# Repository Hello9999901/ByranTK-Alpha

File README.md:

# ByranTK-Alpha

# Note: New 3D Printed Version of the case added! First prototype working!!

*The ByranTK-Alpha is an 80 key custom mechanical keyboard, designed to be made with any material.*
<br>
<br>
*"All the keys you need and no more."*

### V1.1 is confirmed to be working with firmware from https://github.com/Hello9999901/zmk-config-btk-alpha

# What is it:
The ByranTK-Alpha is an ongoing open-source keyboard project. It is extremely simple and utilizes a nice!nano from Nice Keyboards as the MCU. The battery life is estimated to be around 3 months of continuous usage (varies extremely depending on battery capacity, tested with 500mah battery from Adafruit). The keyboard is designed in KiCAD and FreeCAD, with the renders made with Blender.

# Features:
 - ZMK Firmware
 - Pro Micro Form Factor *
 - Wireless First Design
 - Split Spacebar
 - Low Profile (relative to other keyboards)
 - Hotswap Sockets
 - South facing (supports cherry profile)
 - Exploded 75% (ish) layout
 - Highly Customizable

# Why?
Because nobody has done such thing yet. I have always wanted a simple-looking, customizable (software-wise and hardware-wise), exploded 75% layout keyboard. In addition, it had to be under a certain price point. I estimate for it to cost less than 100 dollars for all the parts and all the machining, though that is subject to change. If you want CNC alu, then that'll cost you a couple cold hard Benjamins (tldr; a lot).

# Image Gallery
(subject to change as design alters)
<div style="display: flex;">

</div>

# Build Guide
### This build guide is very vague and will be improved on in the near future
### Parts:
> Note that these part links are only for reference. Some products can be found for cheaper (especially the hotswap sockets).

> The SPDT and SPST switches have specific footprints that match on the board. You can alter them if they're out of stock.

> You don't need to buy diodes if you are using SMT assembly. I used JLCPCB.
  - PCB
  - [Kailh Hotswap Sockets](https://shop.keyboard.io/products/kailh-hotswap-sockets-for-mx-style-keyswitches-x-25)
  - [Diodes (1N4148 SMT SOD-123)](https://www.adafruit.com/product/5099)
  - [SPDT Switch](https://www.adafruit.com/product/805)
  - [Battery (can be different capacity) with JST-PH 2 Pin Header](https://www.adafruit.com/product/1578)
  - [SPST Switch](https://www.adafruit.com/product/1489)
  - [JST-PH Right Angle Connector](https://www.adafruit.com/product/1769)
  - [Swiss Socket Headers (Female)](https://www.adafruit.com/product/3646)
  - [Swiss Socket Headers (Male)](https://www.adafruit.com/product/3647)

1. Order all the parts
   - I ordered everything off of JLCPCB, with SMT assembly for the diodes because I'm lazy. The pick and place/bom files are in the bom folder, ready for upload to JLCPCB. It is highly suggested you use SMT assembly because it is extremely cheap and saves a lot of time.
   - Apparantly, you can also get smt hotswap sockets assembled too, though I did not do that.
2. Solder it all together
   - Solder on the hotswap sockets and the nice!nano. This will take a while (perhaps an hour or two) depending on your soldering experience. Note that if you choose not to use SMT assembly on the PCB, the diodes will be very hard to solder. I socketed the nice!nano using Swiss machine pins off of Adafruit.
3. Build and flash the firmware onto the nice!nano
   - Build the firmware and put the nice!nano into bootloader (DFU) mode (short GND and RST twice in rapid succession). Drag the UF2 file into the nice!nano "storage device". The firmware can be made with my zmk-config directory.
4. Laser cut the case or 3D print
   - This step is pretty self explanatory. It's a sandwich design, so lasercut many pieces and adhere them together. The plate must be 1.5mm (+- 0.1mm). The rest can be any height as long as when everything is stacked together, it is taller than 15mm, and the height between the bottom of the plate and the top of the bottom pice is taller than 12mm.
   - Alternatively, you can 3D print the case. I decided to 3D print because it was faster to prototype. 2 file types, one split and one full depending on your bed size. It also looks really cool.
5. Put everything together
   - Glue it, screw it together, I don't really know. I screwed into a 3D printed case with some screws found in a bin of hope. Just make sure the entire thing fits. If you're that type of person, the more FLeX the better. Nylon should get you that. Plug in the battery (you might need to switch the battery wiring to make sure the GND goes into GND and RAW goes into RAW). You don't need screws to hold the PCB and plate together; the hotswap sockets and the plate should hold itself together. Get some 5mm foam and put it as dampener under the PCB. Make sure to keep the battery isolated when dampening so it doesn't short/blow up.
6. Use it
   - You've made it! Congrats! Customize the keymap, change the case material, it's all up to you. That's the beauty of open source hardware and software. I hope you enjoy the ByranTK-Alpha.

# License
Unless stated otherwise, the parts are licensed under the MIT License. Parts that are identified as (GPL) are licensed under the GPLv3 License.

\* The nice!nano v2 is used in this design. It has 3 extra pins in the center of the PCB, two of which the ByranTK-Alpha utilizes

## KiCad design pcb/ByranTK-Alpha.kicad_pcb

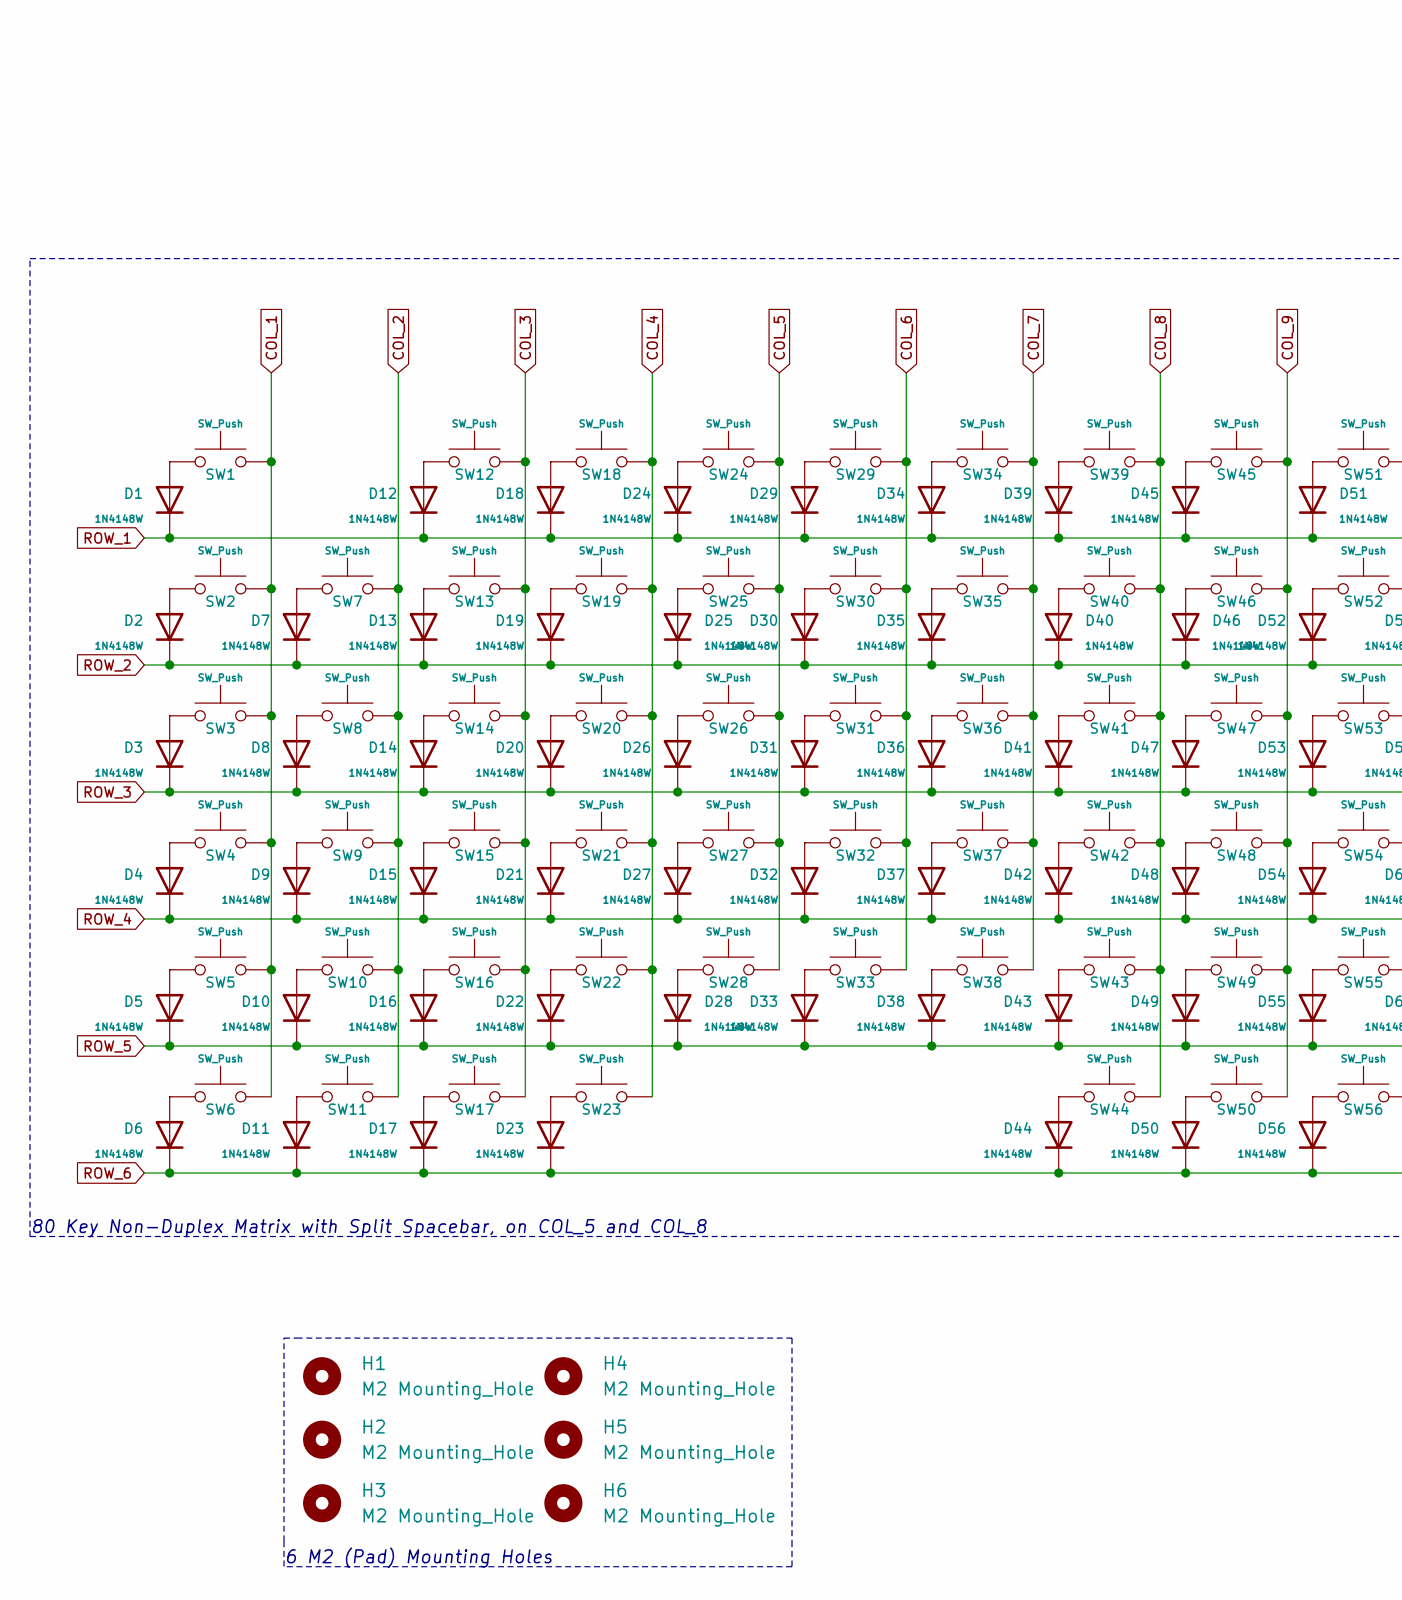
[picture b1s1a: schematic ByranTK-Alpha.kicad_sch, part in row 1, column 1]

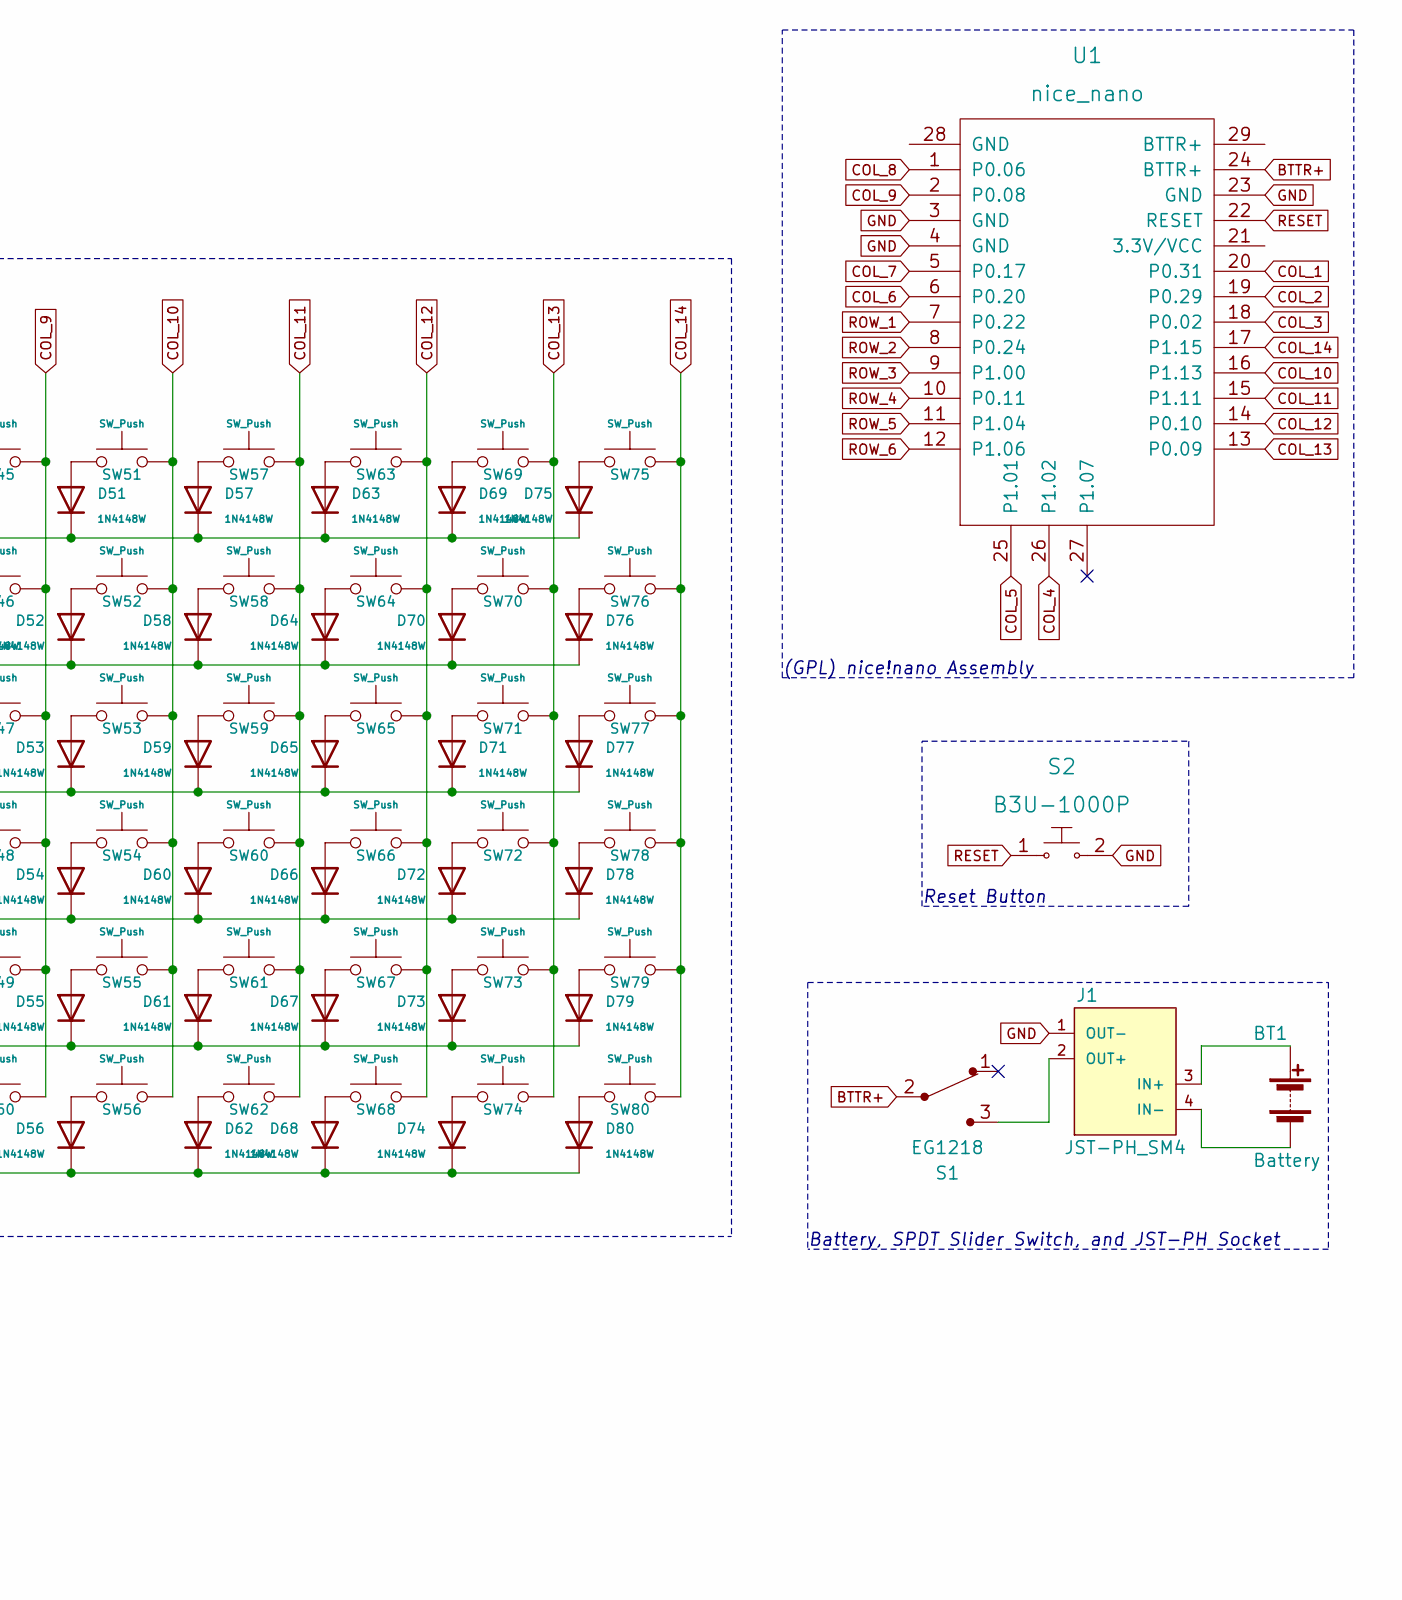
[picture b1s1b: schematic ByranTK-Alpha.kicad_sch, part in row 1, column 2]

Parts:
BT1: Battery; ADAFRUIT_BAT_ID_1570_100mAh
D1, D2, D3, D4, D5, D6, D7, D8, D9, D10, D11, D12, D13, D14, D15, D16, D17, D18, D19, D20, D21, D22, D23, D24, D25, D26, D27, D28, D29, D30, D31, D32, D33, D34, D35, D36, D37, D38, D39, D40, D41, D42, D43, D44, D45, D46, D47, D48, D49, D50, D51, D52, D53, D54, D55, D56, D57, D58, D59, D60, D61, D62, D63, D64, D65, D66, D67, D68, D69, D70, D71, D72, D73, D74, D75, D76, D77, D78, D79, D80: 1N4148W; D_SOD-123
H1, H2, H3, H4, H5, H6: M2 Mounting_Hole; MountingHole_2.2mm_M2_Pad
J1: JST-PH_SM4; JST_PH_S2B-PH-SM4-TB_1x02-1MP_P2.00mm_Horizontal
S1: EG1218; Switch_Slide_11.6x4mm_EG1218; MPN EG1218; Digi-Key_PN EG1903-ND
S2: B3U-1000P; Switch_Tactile_SMD_B3U-1000P; MPN B3U-1000P; Digi-Key_PN SW1020CT-ND
SW1, SW2, SW7, SW8, SW9, SW10, SW12, SW13, SW14, SW15, SW16, SW18, SW19, SW20, SW21, SW22, SW24, SW25, SW26, SW27, SW28, SW29, SW30, SW31, SW32, SW33, SW34, SW35, SW36, SW37, SW38, SW39, SW40, SW41, SW42, SW43, SW45, SW46, SW47, SW48, SW49, SW50, SW51, SW52, SW53, SW54, SW55, SW56, SW57, SW58, SW59, SW60, SW61, SW62, SW63, SW64, SW65, SW66, SW68, SW69, SW70, SW71, SW73, SW74, SW75, SW78, SW79, SW80: SW_Push; MXOnly-1U-Hotswap
SW3, SW77: SW_Push; MXOnly-1.5U-Hotswap
SW4, SW67: SW_Push; MXOnly-1.75U-Hotswap
SW5, SW72: SW_Push; MXOnly-2.25U-Hotswap
SW6, SW11, SW17: SW_Push; MXOnly-1.25U-Hotswap
SW23, SW44: SW_Push; MXOnly-2.75U-Hotswap
SW76: SW_Push; MXOnly-2U-Hotswap
U1: nice_nano

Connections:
BTTR+: S1.2, U1.24 (BTTR+)
COL_1: SW1.2, SW2.2, SW3.2, SW4.2, SW5.2, SW6.2, U1.20 (P0.31)
COL_2: SW7.2, SW8.2, SW9.2, SW10.2, SW11.2, U1.19 (P0.29)
COL_3: SW12.2, SW13.2, SW14.2, SW15.2, SW16.2, SW17.2, U1.18 (P0.02)
COL_4: SW18.2, SW19.2, SW20.2, SW21.2, SW22.2, SW23.2, U1.26 (P1.02)
COL_5: SW24.2, SW25.2, SW26.2, SW27.2, SW28.2, U1.25 (P1.01)
COL_6: SW29.2, SW30.2, SW31.2, SW32.2, SW33.2, U1.6 (P0.20)
COL_7: SW34.2, SW35.2, SW36.2, SW37.2, SW38.2, U1.5 (P0.17)
COL_8: SW39.2, SW40.2, SW41.2, SW42.2, SW43.2, SW44.2, U1.1 (P0.06)
COL_9: SW45.2, SW46.2, SW47.2, SW48.2, SW49.2, SW50.2, U1.2 (P0.08)
COL_10: SW51.2, SW52.2, SW53.2, SW54.2, SW55.2, SW56.2, U1.16 (P1.13)
COL_11: SW57.2, SW58.2, SW59.2, SW60.2, SW61.2, SW62.2, U1.15 (P1.11)
COL_12: SW63.2, SW64.2, SW65.2, SW66.2, SW67.2, SW68.2, U1.14 (P0.10)
COL_13: SW69.2, SW70.2, SW71.2, SW72.2, SW73.2, SW74.2, U1.13 (P0.09)
COL_14: SW75.2, SW76.2, SW77.2, SW78.2, SW79.2, SW80.2, U1.17 (P1.15)
GND: J1.1 (OUT-), S2.2, U1.3 (GND), U1.4 (GND), U1.23 (GND)
unnamed: D1.2 (A), SW1.1
unnamed: D2.2 (A), SW2.1
unnamed: D3.2 (A), SW3.1
unnamed: D4.2 (A), SW4.1
unnamed: D5.2 (A), SW5.1
unnamed: D6.2 (A), SW6.1
unnamed: D7.2 (A), SW7.1
unnamed: D8.2 (A), SW8.1
unnamed: D9.2 (A), SW9.1
unnamed: D10.2 (A), SW10.1
unnamed: D11.2 (A), SW11.1
unnamed: D12.2 (A), SW12.1
unnamed: D13.2 (A), SW13.1
unnamed: D14.2 (A), SW14.1
unnamed: D15.2 (A), SW15.1
unnamed: D16.2 (A), SW16.1
unnamed: D17.2 (A), SW17.1
unnamed: D18.2 (A), SW18.1
unnamed: D19.2 (A), SW19.1
unnamed: D20.2 (A), SW20.1
unnamed: D21.2 (A), SW21.1
unnamed: D22.2 (A), SW22.1
unnamed: D23.2 (A), SW23.1
unnamed: D24.2 (A), SW24.1
unnamed: D25.2 (A), SW25.1
unnamed: D26.2 (A), SW26.1
unnamed: D27.2 (A), SW27.1
unnamed: D28.2 (A), SW28.1
unnamed: D29.2 (A), SW29.1
unnamed: D30.2 (A), SW30.1
unnamed: D31.2 (A), SW31.1
unnamed: D32.2 (A), SW32.1
unnamed: D33.2 (A), SW33.1
unnamed: D34.2 (A), SW34.1
unnamed: D35.2 (A), SW35.1
unnamed: D36.2 (A), SW36.1
unnamed: D37.2 (A), SW37.1
unnamed: D38.2 (A), SW38.1
unnamed: D39.2 (A), SW39.1
unnamed: D40.2 (A), SW40.1
unnamed: D41.2 (A), SW41.1
unnamed: D42.2 (A), SW42.1
unnamed: D43.2 (A), SW43.1
unnamed: D44.2 (A), SW44.1
unnamed: D45.2 (A), SW45.1
unnamed: D46.2 (A), SW46.1
unnamed: D47.2 (A), SW47.1
unnamed: D48.2 (A), SW48.1
unnamed: D49.2 (A), SW49.1
unnamed: D50.2 (A), SW50.1
unnamed: D51.2 (A), SW51.1
unnamed: D52.2 (A), SW52.1
unnamed: D53.2 (A), SW53.1
unnamed: D54.2 (A), SW54.1
unnamed: D55.2 (A), SW55.1
unnamed: D56.2 (A), SW56.1
unnamed: D57.2 (A), SW57.1
unnamed: D58.2 (A), SW58.1
unnamed: D59.2 (A), SW59.1
unnamed: D60.2 (A), SW60.1
unnamed: D61.2 (A), SW61.1
unnamed: D62.2 (A), SW62.1
unnamed: D63.2 (A), SW63.1
unnamed: D64.2 (A), SW64.1
unnamed: D65.2 (A), SW65.1
unnamed: D66.2 (A), SW66.1
unnamed: D67.2 (A), SW67.1
unnamed: D68.2 (A), SW68.1
unnamed: D69.2 (A), SW69.1
unnamed: D70.2 (A), SW70.1
unnamed: D71.2 (A), SW71.1
unnamed: D72.2 (A), SW72.1
unnamed: D73.2 (A), SW73.1
unnamed: D74.2 (A), SW74.1
unnamed: D75.2 (A), SW75.1
unnamed: D76.2 (A), SW76.1
unnamed: D77.2 (A), SW77.1
unnamed: D78.2 (A), SW78.1
unnamed: D79.2 (A), SW79.1
unnamed: D80.2 (A), SW80.1
unnamed: J1.2 (OUT+), S1.3
RESET: S2.1, U1.22 (RESET)
ROW_1: D1.1 (K), D12.1 (K), D18.1 (K), D24.1 (K), D29.1 (K), D34.1 (K), D39.1 (K), D45.1 (K), D51.1 (K), D57.1 (K), D63.1 (K), D69.1 (K), D75.1 (K), U1.7 (P0.22)
ROW_2: D2.1 (K), D7.1 (K), D13.1 (K), D19.1 (K), D25.1 (K), D30.1 (K), D35.1 (K), D40.1 (K), D46.1 (K), D52.1 (K), D58.1 (K), D64.1 (K), D70.1 (K), D76.1 (K), U1.8 (P0.24)
ROW_3: D3.1 (K), D8.1 (K), D14.1 (K), D20.1 (K), D26.1 (K), D31.1 (K), D36.1 (K), D41.1 (K), D47.1 (K), D53.1 (K), D59.1 (K), D65.1 (K), D71.1 (K), D77.1 (K), U1.9 (P1.00)
ROW_4: D4.1 (K), D9.1 (K), D15.1 (K), D21.1 (K), D27.1 (K), D32.1 (K), D37.1 (K), D42.1 (K), D48.1 (K), D54.1 (K), D60.1 (K), D66.1 (K), D72.1 (K), D78.1 (K), U1.10 (P0.11)
ROW_5: D5.1 (K), D10.1 (K), D16.1 (K), D22.1 (K), D28.1 (K), D33.1 (K), D38.1 (K), D43.1 (K), D49.1 (K), D55.1 (K), D61.1 (K), D67.1 (K), D73.1 (K), D79.1 (K), U1.11 (P1.04)
ROW_6: D6.1 (K), D11.1 (K), D17.1 (K), D23.1 (K), D44.1 (K), D50.1 (K), D56.1 (K), D62.1 (K), D68.1 (K), D74.1 (K), D80.1 (K), U1.12 (P1.06)

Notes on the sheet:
80 Key Non-Duplex Matrix with Split Spacebar, on COL_5 and COL_8
6 M2 (Pad) Mounting Holes
(GPL) nice!nano Assembly
Battery, SPDT Slider Switch, and JST-PH Socket
Reset Button

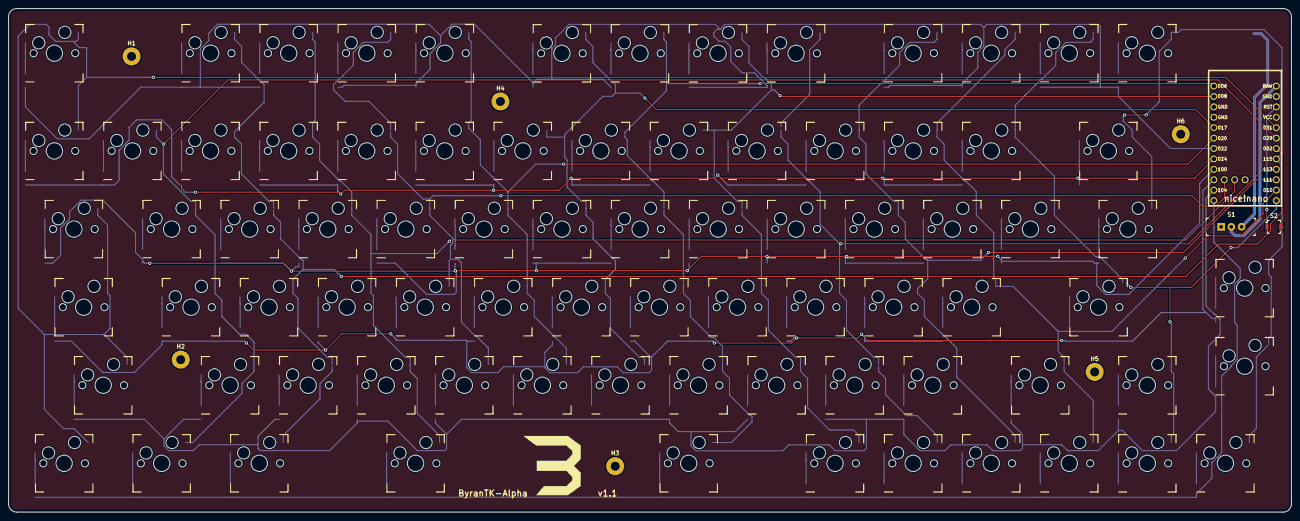
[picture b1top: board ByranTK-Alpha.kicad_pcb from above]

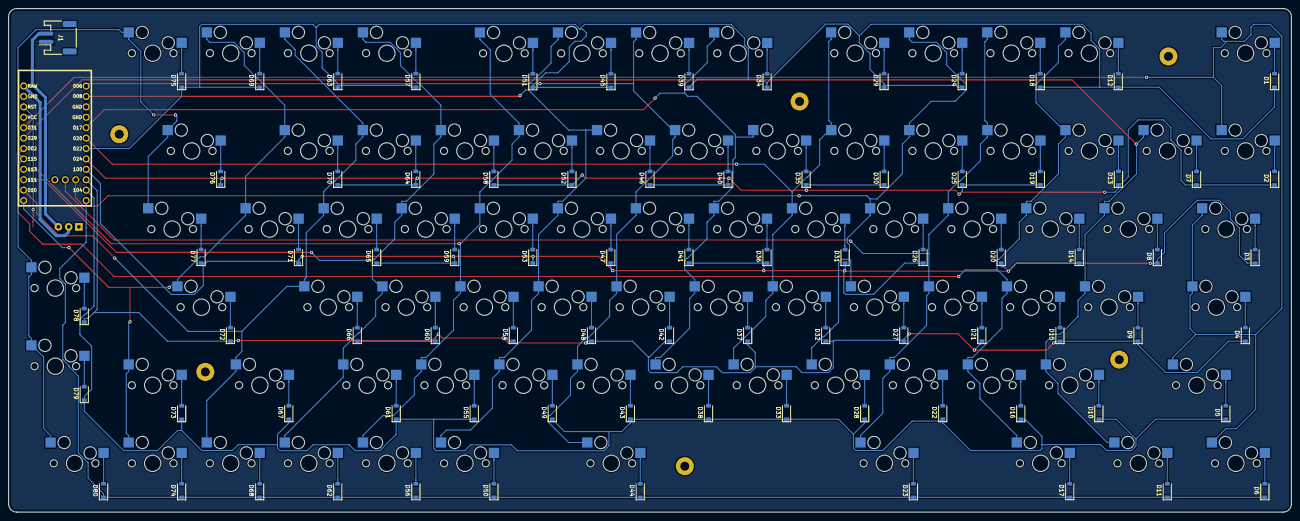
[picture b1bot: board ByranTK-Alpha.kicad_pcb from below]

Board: 2 copper layers, 313.0 x 122.9 mm, 171 parts (82 on the bottom side), 104 nets.

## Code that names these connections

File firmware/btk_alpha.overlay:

#include <dt-bindings/zmk/matrix_transform.h>

/ {
    chosen {
        zmk,kscan = &kscan0;
        zmk,matrix_transform = &default_transform;
    };

    default_transform: keymap_transform_0 {
        compatible = "zmk,matrix-transform";
        columns = <14>;
        rows = <6>;
        map = <
    RC(0,0)          RC(0,2) RC(0,3) RC(0,4) RC(0,5)    RC(0,6) RC(0,7) RC(0,8) RC(0,9)      RC(0,10) RC(0,11) RC(0,12) RC(0,13)
    RC(1,0)  RC(1,1) RC(1,2) RC(1,3) RC(1,4) RC(1,5) RC(1,6) RC(1,7) RC(1,8) RC(1,9) RC(1,10) RC(1,11) RC(1,12)     RC(1,13)
    RC(2,0)    RC(2,1) RC(2,2) RC(2,3) RC(2,4) RC(2,5) RC(2,6) RC(2,7) RC(2,8) RC(2,9) RC(2,10) RC(2,11) RC(2,12)   RC(2,13)
    RC(3,0)     RC(3,1) RC(3,2) RC(3,3) RC(3,4) RC(3,5) RC(3,6) RC(3,7) RC(3,8) RC(3,9) RC(3,10) RC(3,11)      RC(3,12)       RC(3, 13)
    RC(4,0)       RC(4,1) RC(4,2) RC(4,3) RC(4,4) RC(4,5) RC(4,6) RC(4,7) RC(4,8) RC(4,9) RC(4,10)    RC(4,11)       RC(4,12) RC(4,13)
    RC(5,0)    RC(5,1)   RC(5,2)           RC(5,3)              RC(5,7)     RC(5,8)    RC(5,9)  RC(5,10)    RC(5,11) RC(5,12) RC(5,13)
        >;
    };
    kscan0: kscan_0 {
        compatible = "zmk,kscan-gpio-matrix";
        label = "KSCAN";
        diode-direction = "col2row";

        col-gpios
            = <&pro_micro 21 GPIO_ACTIVE_HIGH> //COL_1  D21
            , <&pro_micro 20 GPIO_ACTIVE_HIGH> //COL_2  D20
            , <&pro_micro 19 GPIO_ACTIVE_HIGH> //COL_3  D19
            , <&gpio1 2 GPIO_ACTIVE_HIGH>      //COL_4  P1.02
            , <&gpio1 1 GPIO_ACTIVE_HIGH>      //COL_5  P1.01
            , <&pro_micro 3 GPIO_ACTIVE_HIGH>  //COL_6  D3
            , <&pro_micro 2 GPIO_ACTIVE_HIGH>  //COL_7  D2
            , <&pro_micro 1 GPIO_ACTIVE_HIGH>  //COL_8  D1
            , <&pro_micro 0 GPIO_ACTIVE_HIGH> //COL_9   D0
            , <&pro_micro 15 GPIO_ACTIVE_HIGH> //COL_10 D15
            , <&pro_micro 14 GPIO_ACTIVE_HIGH> //COL_11 D14
            , <&pro_micro 16 GPIO_ACTIVE_HIGH> //COL_12 D16
            , <&pro_micro 10 GPIO_ACTIVE_HIGH> //COL_13 D10
            , <&pro_micro 18 GPIO_ACTIVE_HIGH> //COL_14 D18
            ;

        row-gpios
            = <&pro_micro 4 (GPIO_ACTIVE_HIGH | GPIO_PULL_DOWN)> //ROW_1 D4
            , <&pro_micro 5 (GPIO_ACTIVE_HIGH | GPIO_PULL_DOWN)> //ROW_2 D5
            , <&pro_micro 6 (GPIO_ACTIVE_HIGH | GPIO_PULL_DOWN)> //ROW_3 D6
            , <&pro_micro 7 (GPIO_ACTIVE_HIGH | GPIO_PULL_DOWN)> //ROW_4 D7
            , <&pro_micro 8 (GPIO_ACTIVE_HIGH | GPIO_PULL_DOWN)> //ROW_5 D8
            , <&pro_micro 9 (GPIO_ACTIVE_HIGH | GPIO_PULL_DOWN)> //ROW_6 D9
            ;
    };
};

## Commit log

2021-09-12 pcb upload
2021-09-12 added images
2021-10-26 fixes
2021-10-26 replaced images
2021-11-22 revision 1.1
2021-12-19 updated to v1.1
2021-12-19 added bom and stuff
2021-12-20 added case dxf files
2021-12-20 added pick and place/bom/ibom
2021-12-20 added build guide
2021-12-20 added firmware onto repo
2021-12-20 update parts
2021-12-23 updated case files (switched ai to dxf, sorry!) will convert back to dxf later.
2022-03-25 price change bc things aren't as expensive as I thought despite silicon shortage sadge
2022-03-27 refactor + debug firmware
2022-05-23 updated to kicad 6.99 (7)

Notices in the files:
pcb/ByranTK-Alpha.kicad_pcb:
https://opensource.org/licenses/MIT and https://www.gnu.org/licenses/gpl-3.0.en.html
GNU GPLv3 license. The sections are idendified in the README.
License: Various sections are licensed either under the MIT License or the
